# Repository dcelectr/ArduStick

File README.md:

# ArduStick
Arduino compatible board (ATmega 328P) for breadboards or small projects where space is limited.
The J3 through J5 are intended to be populated by a single row 23 pin female socket, but it can be substituted (since the footprint is the same for 0.1" pin spacing) with 90 degree (horizontal) male header if you want to plug the ArduStick directly on a breadboard.
This design has been built and tested. It works!

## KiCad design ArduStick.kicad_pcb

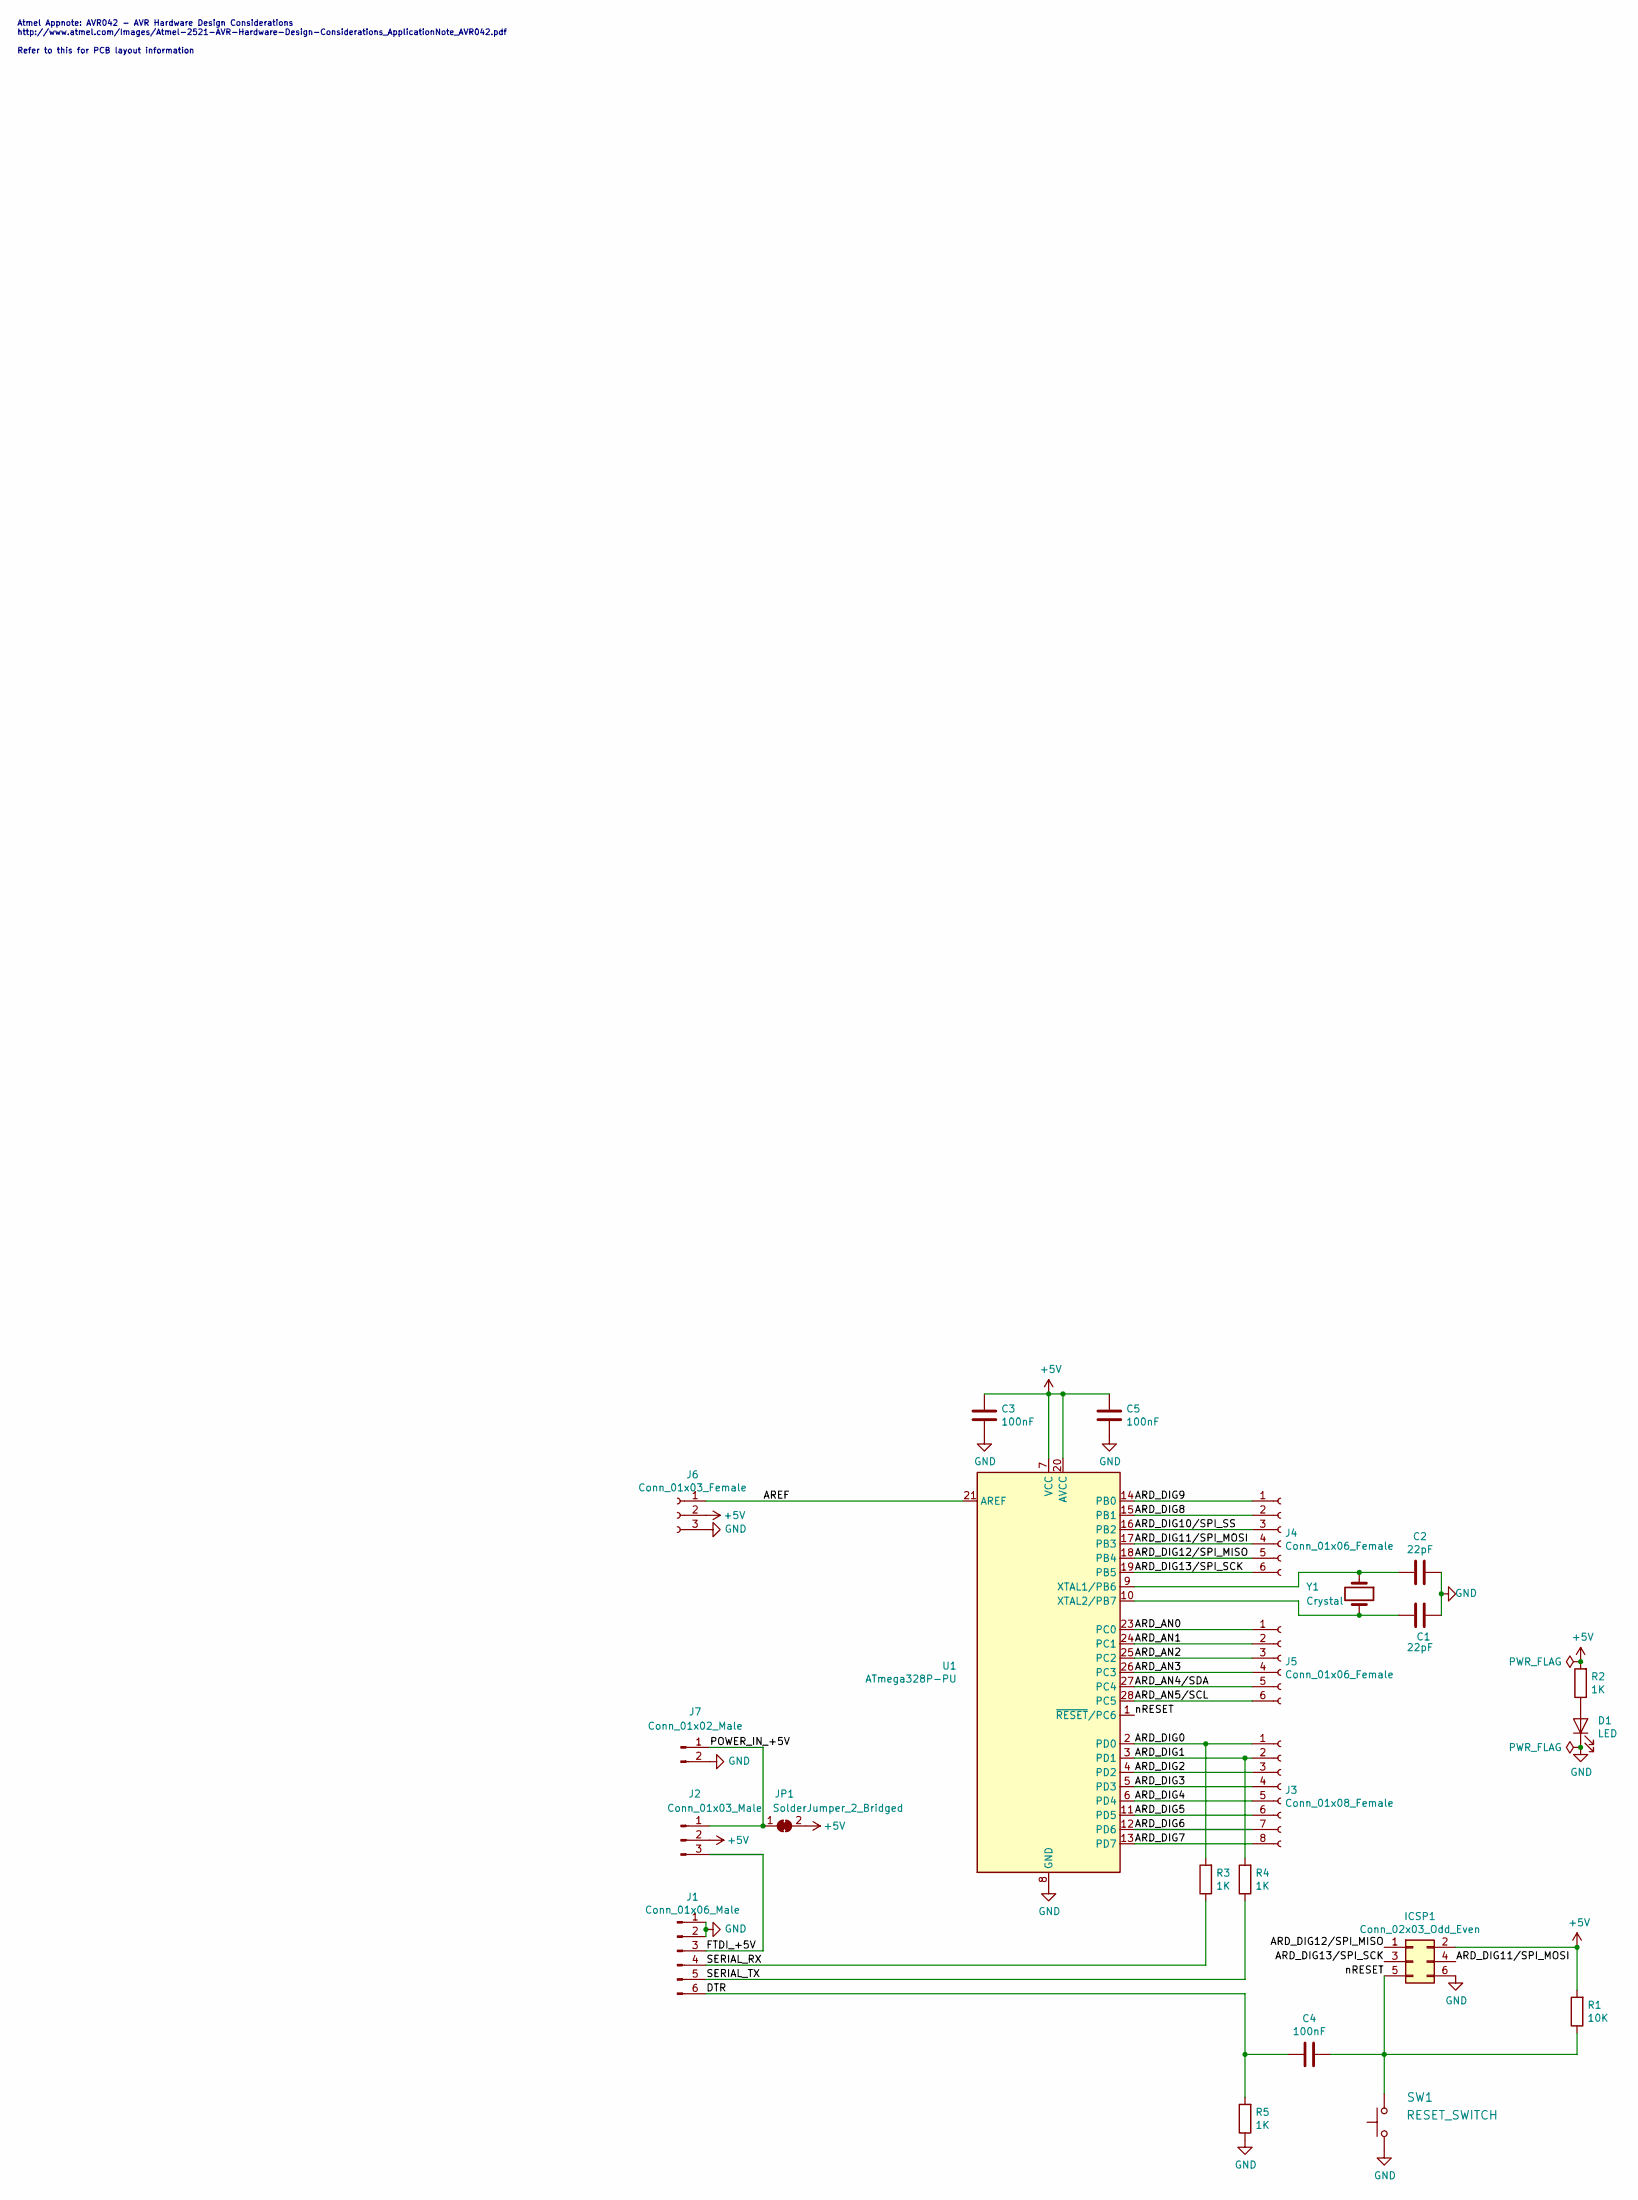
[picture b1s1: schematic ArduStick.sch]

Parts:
C1, C2: 22pF; C_Disc_D3.0mm_W1.6mm_P2.50mm
C3, C4, C5: 100nF; C_Disc_D3.0mm_W1.6mm_P2.50mm
D1: LED; LED_D3.0mm
ICSP1: Conn_02x03_Odd_Even; PinHeader_2x03_P2.54mm_Vertical
J1: Conn_01x06_Male; PinHeader_1x06_P2.54mm_Vertical
J2: Conn_01x03_Male; PinHeader_1x03_P2.54mm_Vertical
J3: Conn_01x08_Female; PinSocket_1x08_P2.54mm_Vertical
J4, J5: Conn_01x06_Female; PinSocket_1x06_P2.54mm_Vertical
J6: Conn_01x03_Female; PinSocket_1x03_P2.54mm_Vertical
J7: Conn_01x02_Male; PinHeader_1x02_P2.54mm_Vertical
JP1: SolderJumper_2_Bridged; SolderJumper-2_P1.3mm_Bridged_RoundedPad1.0x1.5mm
R1: 10K; R_Axial_DIN0204_L3.6mm_D1.6mm_P5.08mm_Horizontal
R2, R3, R4, R5: 1K; R_Axial_DIN0204_L3.6mm_D1.6mm_P5.08mm_Horizontal
SW1: RESET_SWITCH; SW_PUSH_6mm
U1: ATmega328P-PU; DIP-28_W7.62mm
Y1: Crystal; Crystal_HC49-4H_Vertical

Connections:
+5V: C3.1, C5.1, ICSP1.2, J2.2, J6.2, JP1.2 (B), R1.2, R2.2, U1.7 (VCC), U1.20 (AVCC)
/ARD_AN0: J5.1, U1.23 (PC0)
/ARD_AN1: J5.2, U1.24 (PC1)
/ARD_AN2: J5.3, U1.25 (PC2)
/ARD_AN3: J5.4, U1.26 (PC3)
/ARD_AN4/SDA: J5.5, U1.27 (PC4)
/ARD_AN5/SCL: J5.6, U1.28 (PC5)
/ARD_DIG0: J3.1, R3.2, U1.2 (PD0)
/ARD_DIG1: J3.2, R4.2, U1.3 (PD1)
/ARD_DIG2: J3.3, U1.4 (PD2)
/ARD_DIG3: J3.4, U1.5 (PD3)
/ARD_DIG4: J3.5, U1.6 (PD4)
/ARD_DIG5: J3.6, U1.11 (PD5)
/ARD_DIG6: J3.7, U1.12 (PD6)
/ARD_DIG7: J3.8, U1.13 (PD7)
/ARD_DIG8: J4.2, U1.15 (PB1)
/ARD_DIG9: J4.1, U1.14 (PB0)
/ARD_DIG10/SPI_SS: J4.3, U1.16 (PB2)
/ARD_DIG11/SPI_MOSI: ICSP1.4, J4.4, U1.17 (PB3)
/ARD_DIG12/SPI_MISO: ICSP1.1, J4.5, U1.18 (PB4)
/ARD_DIG13/SPI_SCK: ICSP1.3, J4.6, U1.19 (PB5)
/AREF: J6.1, U1.21 (AREF)
/DTR: C4.2, J1.6, R5.2
/FTDI_+5V: J1.3, J2.3
/POWER_IN_+5V: J2.1, J7.1, JP1.1 (A)
/SERIAL_RX: J1.4, R3.1
/SERIAL_TX: J1.5, R4.1
/nRESET: C4.1, ICSP1.5, R1.1, SW1.2, U1.1 (~RESET~/PC6)
GND: C1.1, C2.1, C3.2, C5.2, D1.1 (K), ICSP1.6, J1.1, J1.2, J6.3, J7.2, R5.1, SW1.1, U1.8 (GND), U1.22 (GND)
unnamed: C1.2, U1.10 (XTAL2/PB7), Y1.2
unnamed: C2.2, U1.9 (XTAL1/PB6), Y1.1
unnamed: D1.2 (A), R2.1

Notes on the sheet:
Atmel Appnote: AVR042 - AVR Hardware Design Considerations http://www.atmel.com/Images/Atmel-2521-AVR-Hardware-Design-Considerations_ApplicationNote_AVR042.pdf Refer to this for PCB layout information

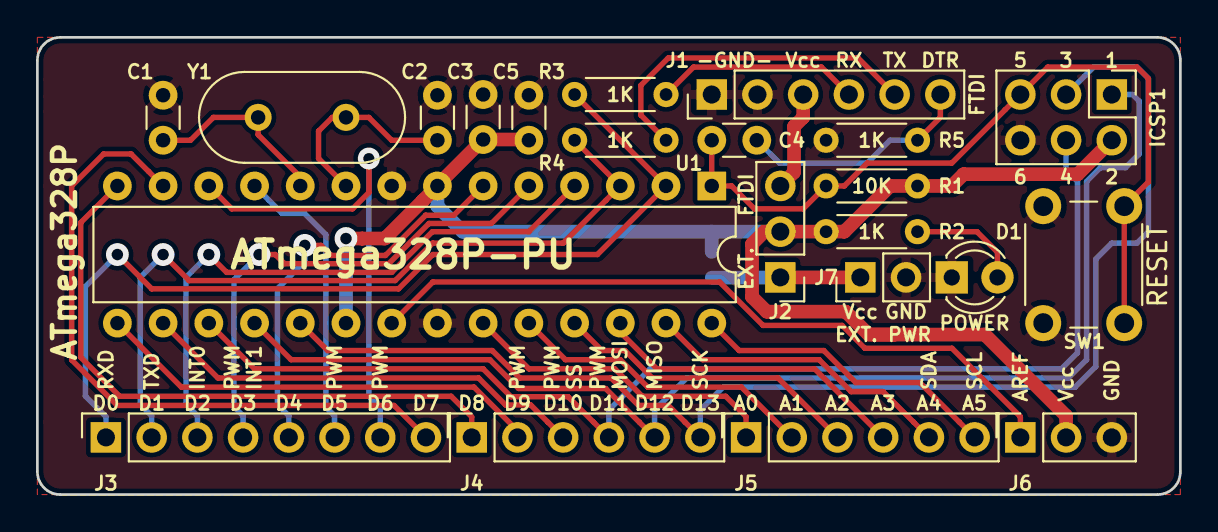
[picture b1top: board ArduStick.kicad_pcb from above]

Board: 2 copper layers, 63.5 x 25.4 mm, 23 parts (1 on the bottom side), 32 nets.

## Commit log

2019-04-01 Create LICENSE,md
2019-07-09 3D renderings
    The J3 through J5 female sockets can be substituted (since the footprint is the same for 0.1" pin spacing) by 90 degree (horizontal) male headers if you want to plug the Ardustick directly on a bread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
2020-12-17 Added Bill of Materials CSV file
